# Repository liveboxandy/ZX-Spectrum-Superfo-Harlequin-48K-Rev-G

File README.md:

This is a Kicad 10 project and was only used to create an ibom to assist in the debugging of faulty boards. Use at your own risk.

This was done by Importing the Orcad files into Altium, saving as Altium files and then importing those files into Kicad.

I have not created any Gerbers from this and would advise anyone to use the original gerbers.

I found the Orcad files at https://8bit-wiki.de/Sinclair/ZX_Spectrum/_zx48/SONSTIGES/harlequin/harlequin_rev-g.zip

The zip file also contains gerber files. I do not know if these are the original gerbers that are on PCBWay.

More information is available at https://8bit-wiki.de/Sinclair/ZX_Spectrum/_zx48/SONSTIGES/harlequin/ including a binary file of the ROM as well as information on building the Rev F.

Have fun.

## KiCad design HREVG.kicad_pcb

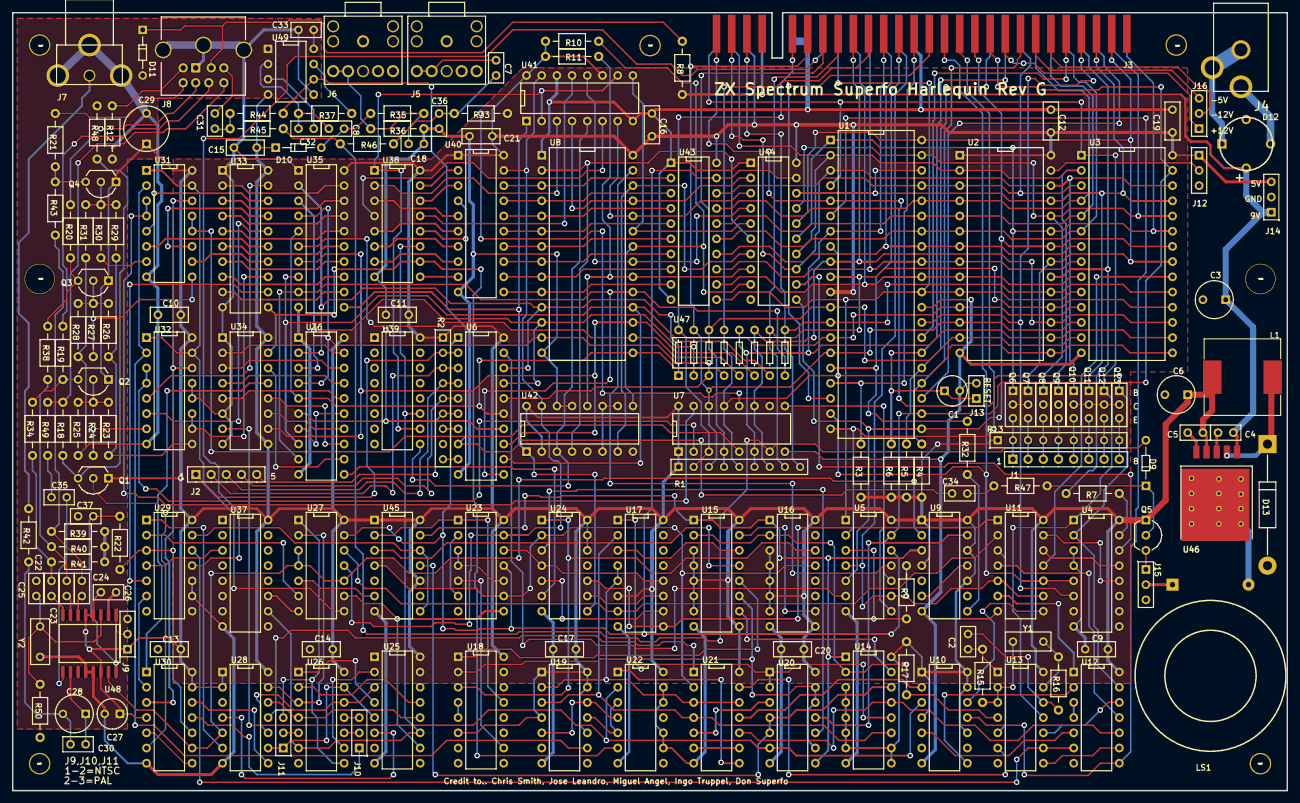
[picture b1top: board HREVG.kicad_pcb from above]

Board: 2 copper layers, 213.0 x 130.0 mm, 180 parts (0 on the bottom side), 272 nets.

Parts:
C1, C27: 10uF; .031
C2: 100pF; .031
C3: 680uF; .031
C4, C5, C7, C8, C9, C10, C11, C12, C13, C14, C15, C16, C17, C19, C20, C21, C22, C23, C24, C26, C30, C31, C33, C34: 0.1uF; .031
C6, C28, C29: 220uF; .031
C18, C32: 1nF; .031
C25, C37: 10pF; .031
C35, C36: 3.3nF; .031
D9: 1N4148; .028
D10: 1N4740A; .028
D11: 1N4742A; .028
D12: BRIDGE; BRIDGE DIODE
D13: 1N5822; .067
H122, H125, H126, H127, H129: HOLE125
H123, H124: HOLE300
J1: RCPT 8; 8
J2: RCPT 5; 5
J3: ZX_EDGE
J4: DC JACK
J5: MIC; AUDIO JACK PSG01538
J6: EAR; AUDIO JACK PSG01538
J7: VIDEO; RCA JACK KY-006-1
J8: M-DIN_8-R; 8
J9, J10, J11, J12, J14, J15, J16: CON3; 3
J13: CON2; 2
L1: 68uH; L_12.8MM
LS1: SPEAKER
Q1, Q2, Q3, Q4, Q5: BC548; 321
Q6, Q7, Q8, Q9, Q10, Q11, Q12, Q13: 2SA1175; TO225
R1, R2: 10K*8; 9
R3, R4, R5, R6, R10, R11, R22, R36: 10K; .034
R7, R9, R15, R16, R32: 470; .034
R8: 150; .034
R12, R18, R48: 270; .034
R13: 4.7K*8; 9
R17: 4K7; .034
R19, R20, R21, R34, R38, R43: 68; .034
R23, R26, R29: 18K; .034
R24, R27, R30: 3.9K; .034
R25, R28, R31: 2.2K; .034
R33: 33K; .034
R35, R45, R46: 12K; .034
R37: 470K; .034
R39, R40, R41, R42: 75; .034
R44: 100K; .034
R47: 22K; .034
R49: 2.7K; .034
R50: 4.7M; .034
U1: Z80-CPU; L2.025
U2: 27C128/27C256; L1.400
U3, U8: 62256; L1.400
U4, U17, U18: 74HC138; L.775
U5, U12, U21, U22, U28: 74HC32; L.700
U6: 74HC541; L.975
U7: 74HC174; L.775
U9, U10, U19, U45: 74HC74; L.700
U11, U24, U26, U29: 74HC08; L.700
U13: 74HC04; L.700
U14, U15, U16: 74HC161; L.775
U20, U23, U27: 74HC00; L.700
U25, U37, U38, U39: 74HC4040; L.775
U30: 74HC86; L.700
U31, U32: 74HC253; L.775
U33, U35, U36: 74HC574; L.975
U34: 74HC166; L.775
U40, U43, U44: 74HC245; L.975
U41, U42: 74HC257; L.775
U46: LM2596; S
U47: RES x 8; RESISTOR DIP 16
U48: AD724JR; L.400
U49: TL712; L.400
Y1: 14MHz; .031
Y2: 4.433MHz; .031

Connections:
+9V: C3.1, C4.1, D12.4, J3.A4, J14.1, R8.1, U46.1
+12V: J3.B22, J16.3
-5V: J3.B20, J16.1
-12V: J3.B23, J16.2
A0: J3.A9, U1.30, U2.10, U3.10, U5.1, U43.11
A1: J3.A10, U1.31, U2.9, U3.9, U43.12
A2: J3.A11, U1.32, U2.8, U3.8, U43.13
A3: J3.A12, U1.33, U2.7, U3.7, U43.14
A4: J3.A24, U1.34, U2.6, U3.6, U43.15
A5: J3.A23, U1.35, U2.5, U3.5, U43.16
A6: J3.A22, U1.36, U2.4, U3.4, U43.17
A7: J3.A21, U1.37, U2.3, U3.3, U43.18
A8: J3.B26, Q11.1, U1.38, U2.25, U3.25, U44.18
A9: J3.A27, Q8.1, U1.39, U2.24, U3.24, U44.17
A10: J3.B27, Q7.1, U1.40, U2.21, U3.21, U44.16
A11: J3.A28, Q6.1, U1.1, U2.23, U3.23, U44.15
A12: J3.A2, Q9.1, U1.2, U2.2, U3.2, U44.14
A13: J3.B2, Q10.1, U1.3, U2.26, U3.26, U44.13
A14: J3.A1, Q12.1, U1.4, U3.1, U4.1, U13.11
A15: J3.B1, Q13.1, U1.5, U4.2, U12.13
AL: U5.12, U6.1, U23.11, U27.13, U43.19, U44.19
AL1: U24.6, U36.11
AL2: U24.8, U35.11, U41.1, U42.1
AUDIO: C31.1, J8.5
B: C22.2, R34.2, R41.1
B0: U7.2, U32.3, U32.4
B1: U7.15, U31.3, U31.4
B2: U7.5, U31.12, U31.13
BLANK: U27.8, U31.1, U31.15, U32.1, U32.15
BUSAK: J3.A26, U1.23
BUSRQ: J3.A19, R5.2, U1.25
C3: U17.12, U23.12, U24.4
C4: U17.11, U24.9
C5: U17.10, U24.5
C6: U11.1, U17.9, U24.10
C7: U11.2, U17.7, U27.12
CA0: U38.9, U40.9
CA1: U38.7, U40.8
CA2: U38.6, U40.7
CA3: U38.5, U40.6
CA4: U38.3, U40.5
CA5: U38.2, U41.3
CA6: U38.4, U41.6
CA7: U38.13, U41.13
CA8: U38.12, U40.4
CA9: U38.14, U40.3
CA10: U38.15, U40.2
CA11: U38.1, U39.10, U41.2, U41.10
CA12: U39.9, U41.5, U42.3
CLK: U1.6, U10.11, U12.8
CLK7: U10.3, U20.6, U22.2, U34.7
CLK14: R17.2, U13.4, U14.2, U15.2, U16.2
CLKB: J3.A8, U29.11
COMSYNC: R22.1, U29.3, U30.10
CSYNC: J8.8, R18.2, R49.1
D0: J3.B6, R1.2, U1.14, U2.11, U3.11, U7.3, U47.16
D1: J3.B7, R1.3, U1.15, U2.12, U3.12, U7.14, U47.15
D2: J3.B8, R1.4, U1.12, U2.13, U3.13, U7.4, U47.14
D3: J3.B11, R1.5, U1.8, U2.15, U3.15, U7.13, U47.13
D4: J3.B12, R1.6, U1.7, U2.16, U3.16, U7.6, U47.12
D5: J3.B10, R1.7, U1.9, U2.17, U3.17, U7.11, U47.11
D6: J3.B9, R1.8, U1.10, U2.18, U3.18, U47.10
D7: J3.B3, R1.9, U1.13, U2.19, U3.19, U47.9
DD0: U32.5, U33.19
DD1: U31.5, U33.18
DD2: U31.11, U33.17
DD3: U32.6, U33.16
DD4: U31.6, U33.15
DD5: U31.10, U33.14
DD6: U32.10, U32.11, U33.13
DD7: U29.5, U33.12
DEN: U17.4, U17.5, U19.2, U21.3, U21.12
EAR: C34.2, R44.2, U6.8, U49.6
G: C23.2, R38.2, R40.1
GND: C1.2, C3.2, C4.2, C5.2, C6.2, C9.2, C10.2, C11.2, C12.2, C13.2, C14.2, C15.2, C16.2, C17.2, C18.2, C19.2, C20.2, C21.2, C25.2, C26.2, C27.2, C29.2, C33.1, C36.2, C37.1, D11.1, D12.2, D13.1, J3.A6, J3.A7, J3.A14, J5.1, J6.1, J7.2, J7.3, J7.4, J8.1, J8.CASE1, J8.CASE2, J8.CASE3, J9.3, J12.3, J13.2, J14.2, J15.3, LS1.2, Q6.2, Q7.2, Q8.2, Q9.2, Q10.2, Q11.2, Q12.2, Q13.2, R25.1, R28.1, R31.1, R36.2, R39.2, R40.2, R41.2, R48.2, R50.2, U1.29, U2.14, U3.14, U4.3, U4.4, U4.8, U5.7, U6.10, U7.8, U8.1, U8.14, U9.7, U10.7, U11.7, U12.7, U13.7, U14.8, U15.8, U16.8, U17.8, U18.4, U18.5, U18.8, U19.7, U20.7, U21.7, U22.7, U22.9, U22.10, U22.12, U22.13, U23.7, U24.7, U25.8, U26.7, U27.7, U28.7, U29.7, U29.9, U29.10, U30.7, U31.8, U32.8, U32.12, U32.13, U33.1, U33.10, U34.1, U34.6, U34.8, U35.1, U35.10, U36.1, U36.10, U37.8, U37.11, U38.8, U39.8, U40.10, U41.8, U41.14, U42.5, U42.6, U42.8, U42.10, U42.11, U42.13, U42.14, U43.1, U43.10, U44.1, U44.10, U45.7, U46.3, U46.5, U46.6, U48.2, U48.12, U48.13, U49.5, Y2.1
HALT: J3.B15, U1.18
HBLANK: U23.8, U25.10, U27.9
HC0: U12.10, U14.13, U21.10
HC1: U14.12, U17.1, U20.1, U20.2
HC2: U14.11, U17.2, U19.3, U21.4
HC3: U15.14, U17.3
HC4: U15.13, U45.3
HC5: U15.12, U18.1
HC6: U15.11, U18.2, U20.9, U20.12, U20.13
HC7: U16.14, U18.3, U24.1
HC8: U16.13, U21.2, U23.9, U24.2, U45.4
HCA: U14.14, U20.4, U20.5, U45.11
HCRST: U9.3, U14.1, U15.1, U16.1, U20.8, U45.13
HQ2: U18.13, U23.1, U45.2
HQ5: U18.10, U23.5
HSYNC: U27.5, U45.6
INT: J3.B13, R32.2, U1.16
IORQ: J3.B17, U1.20, U5.2
IORQULA: J3.A13, R9.2, U5.4, U5.9, U11.5, U11.9
KB0: J2.1, R2.2, U6.2
KB1: J2.2, R2.3, U6.3
KB2: J2.3, R2.4, U6.4
KB3: J2.4, R2.5, U6.5
KB4: J2.5, R2.6, U6.6
M1: J3.B24, U1.27
MIC: R33.1, U7.12
MREQ: J3.B16, U1.19, U4.5, U11.10
N9140174: J1.7, Q12.3, R13.8
N9140178: J1.5, Q10.3, R13.6
N9140216: J1.3, Q8.3, R13.4
N9140220: J1.1, Q6.3, R13.2
N9142338: U4.13, U11.12
N9142396: U4.12, U11.13
N9142452: U23.13, U27.11, U40.19, U41.15, U42.15
N9143526: U5.8, U7.9
N9143600: R2.9, U6.9
N9143688: R2.7, U6.7
N9144766: R32.1, U9.8
N9144948: U9.6, U9.11
N9233740: U5.11, U8.27
N9303187: C2.2, R16.1, U13.12
N9304151: C2.1, R15.2, U13.1
N9317960: R16.2, U13.13, Y1.2
N9321866: R15.1, U13.2, U13.3, Y1.1
N9374757: U14.15, U15.10
N9382027: U15.15, U16.10
N9515493: U20.10, U24.3
N9666460: U21.6, U21.9
N9682608: U20.3, U21.5
N9696999: U21.8, U22.1
N9720175: U19.11, U22.3, U22.5
N9722505: U19.5, U19.12, U22.4
N9871071: U23.2, U23.6
N9877186: U23.3, U23.4, U23.10
N10088701: U9.13, U20.11
N10219220: U11.3, U13.5
N10223960: U13.6, U21.13
N10235603: U10.2, U21.11
N10260341: U12.12, U13.10
N10277668: U11.4, U12.11
N10295566: U10.12, U11.8
N10312093: U11.6, U12.1
N10313402: U10.8, U12.2
N10322108: U12.9, U13.8
N10325691: U12.6, U13.9, U29.12
N10327015: U12.3, U12.4
N10500611: U26.3, U27.2, U28.13
N10526674: J11.2, U26.5
N10528051: J11.3, U26.8, U27.1
N10560042: U10.5, U12.5
N10840289: U30.1, U34.13
N10844000: U29.6, U30.2
N10866414: U30.3, U31.14, U32.14
N11103687: U29.4, U37.3
N11154885: U28.6, U29.1
N11156295: U27.6, U29.2
N11243744: Q3.2, R26.2, R27.2, R28.2
N11255274: R23.1, R26.1, R29.1, U32.9
N11283624: R30.1, U31.7
N11286558: R27.1, U31.9
N11289500: R24.1, U32.7
N11302461: J8.6, R21.2
N11306693: J8.4, R20.2
N11853839: C18.1, J6.4, J6.5, R35.2, R36.1
N12644451: C7.2, J5.4, J5.5
N12745005: J8.7, R19.2
N12754967: D11.2, J8.2, R8.2
N12830653: Q1.1, R18.1, R48.1
N12867715: Q2.1, R19.1, R34.1
N12945953: Q2.2, R23.2, R24.2, R25.2
N12951861: Q4.2, R29.2, R30.2, R31.2
N13352269: C28.1, C30.1, U48.10
N13352313: C24.1, U48.6
N13352489: C22.1, U48.8
N13352497: C37.2, R22.2, U48.16
N13352561: J9.2, U48.1
N13352733: C23.1, U48.7
N13518960: U29.13, U45.8, U45.12
N13904493: R7.2, U4.15
N13930990: D12.1, J4.2, J4.3
N13931214: D12.3, J4.1
N14207378: U5.6, U6.19
N14210330: R9.1, U5.3
N14594312: Q4.1, R21.1, R43.1
N14596045: Q3.1, R20.1, R38.1
N14759031: J10.1, U30.11
N14759035: U28.8, U30.12
N14759061: J10.3, U26.11
N14759091: J10.2, U26.10
N14968302: U33.9, U35.12
N14968306: U33.8, U35.13
N14968310: U33.7, U35.14
N14968314: U33.6, U35.15
N14968318: U33.5, U35.16
N14968322: U33.4, U35.17
N14968326: U33.3, U35.18
N14968330: U33.2, U35.19
N14969564: U34.2, U36.19
N14969568: U34.3, U36.18
N14969572: U34.4, U36.17
N14969576: U34.5, U36.16
N14969580: U34.10, U36.15
N14969584: U34.11, U36.14
N14969588: U34.12, U36.13
N14969592: U34.14, U36.12
N15017545: C28.2, C30.2, R42.1
N15035569: R37.1, U49.7
N15035599: C8.1, C32.1, R37.2, U49.2
N15035847: C32.2, U49.3
N15036534: C8.2, D10.1, R35.1
N15039244: D9.2, Q5.2, R47.1
N15039516: C31.2, R44.1, R45.1
N15072739: J12.2, U2.27
N15109927: D13.2, L1.1, U46.2
N15246346: J7.1, R42.2
N15246924: C35.1, U48.9
N15247173: C35.2, R49.2
N15247511: C7.1, C36.1, R33.2, R46.1
N15262834: J1.2, Q7.3, R13.3
N15262844: J1.4, Q9.3, R13.5
N15262854: J1.6, Q11.3, R13.7
N15262864: J1.8, Q13.3, R13.9
N15287869: J8.3, R12.1
N15289880: J15.1, Q5.1
N15289884: J15.2, LS1.1
N15345365: Q1.2, U30.6
N15345882: U30.5, U30.8
N15353750: C25.1, R50.1, U48.3, Y2.2
N118558201: C34.1, R47.2
NMI: J3.B14, R3.2, U1.17
OUTLATCH: U22.6, U33.11, U34.15, U38.10
R: C24.2, R39.1, R43.2
RAM16: U4.14, U44.12
RAM32: U3.20, U11.11
RD: J3.B18, U1.21, U2.22, U3.22, U5.5, U44.11
RFSH: J3.B25, U1.28, U4.6
ROMCS: J3.A25, R7.1, U2.20
RST: C1.1, J3.A20, J13.1, R6.2, U1.26
SPKR: D9.1, R45.2, R46.2, U7.7
VA0: U8.10, U40.11, U43.9
VA1: U8.9, U40.12, U43.8
VA2: U8.8, U40.13, U43.7
VA3: U8.7, U40.14, U43.6
VA4: U8.6, U40.15, U43.5
VA5: U8.5, U40.16, U43.4
VA6: U8.4, U40.17, U43.3
VA7: U8.3, U40.18, U43.2
VA8: U8.25, U41.4, U44.2
VA9: U8.24, U41.7, U44.3
VA10: U8.21, U41.12, U44.4
VA11: U8.23, U41.9, U44.5
VA12: U8.2, U42.4, U44.6
VA13: U8.26, U42.7, U44.7
VBORDER: U21.1, U28.11
VC2: U25.6, U28.4
VC3: J11.1, U25.5, U26.13, U28.9
VC4: U25.3, U26.12, U28.10
VC5: U25.2, U26.9
VC6: U25.4, U26.1
VC7: U25.13, U26.2
VC8: U25.12, U26.4, U28.12
VCC: C5.1, C6.1, C9.1, C10.1, C11.1, C12.1, C13.1, C14.1, C15.1, C16.1, C17.1, C19.1, C20.1, C21.1, C26.1, C27.1, C29.1, C33.2, D10.2, J3.A3, J9.1, J12.1, J14.3, L1.2, Q1.3, Q2.3, Q3.3, Q4.3, Q5.3, R1.1, R2.1, R3.1, R4.1, R5.1, R6.1, R10.1, R11.1, R12.2, R13.1, R17.1, U1.11, U2.1, U2.28, U3.28, U4.16, U5.14, U6.20, U7.1, U7.16, U8.28, U9.1, U9.4, U9.10, U9.12, U9.14, U10.1, U10.4, U10.10, U10.13, U10.14, U11.14, U12.14, U13.14, U14.3, U14.4, U14.5, U14.6, U14.7, U14.9, U14.10, U14.16, U15.3, U15.4, U15.5, U15.6, U15.7, U15.9, U15.16, U16.3, U16.4, U16.5, U16.6, U16.7, U16.9, U16.16, U17.6, U17.16, U18.6, U18.16, U19.1, U19.4, U19.10, U19.13, U19.14, U20.14, U21.14, U22.14, U23.14, U24.12, U24.13, U24.14, U25.16, U26.14, U27.14, U28.1, U28.2, U28.14, U29.14, U30.4, U30.13, U30.14, U31.16, U32.16, U33.20, U34.9, U34.16, U35.20, U36.20, U37.16, U38.16, U39.16, U40.1, U40.20, U41.11, U41.16, U42.2, U42.16, U43.20, U44.20, U45.1, U45.10, U45.14, U46.4, U48.4, U48.5, U48.14, U49.4, U49.8
VCRST: U25.11, U26.6, U37.10, U38.11, U39.11
VCS: R11.2, U8.20, U42.12, U44.8
VD0: U6.18, U8.11, U35.2, U36.2, U47.1
VD1: U6.17, U8.12, U35.3, U36.3, U47.2
VD2: U6.16, U8.13, U35.4, U36.4, U47.3
VD3: U6.15, U8.15, U35.5, U36.5, U47.4
VD4: U6.14, U8.16, U35.6, U36.6, U47.5
VD5: U6.13, U8.17, U35.7, U36.7, U47.6
VD6: U6.12, U8.18, U35.8, U36.8, U47.7
VD7: U6.11, U8.19, U35.9, U36.9, U47.8
VOUT: U19.9, U31.2, U32.2
VRD: R10.2, U8.22, U42.9, U44.9
VSYNCEN: U9.2, U27.3, U27.4, U27.10, U28.5, U30.9, U48.15
WAIT: J3.B21, R4.2, U1.24
WR: J3.B19, U1.22, U3.27, U5.10, U5.13
